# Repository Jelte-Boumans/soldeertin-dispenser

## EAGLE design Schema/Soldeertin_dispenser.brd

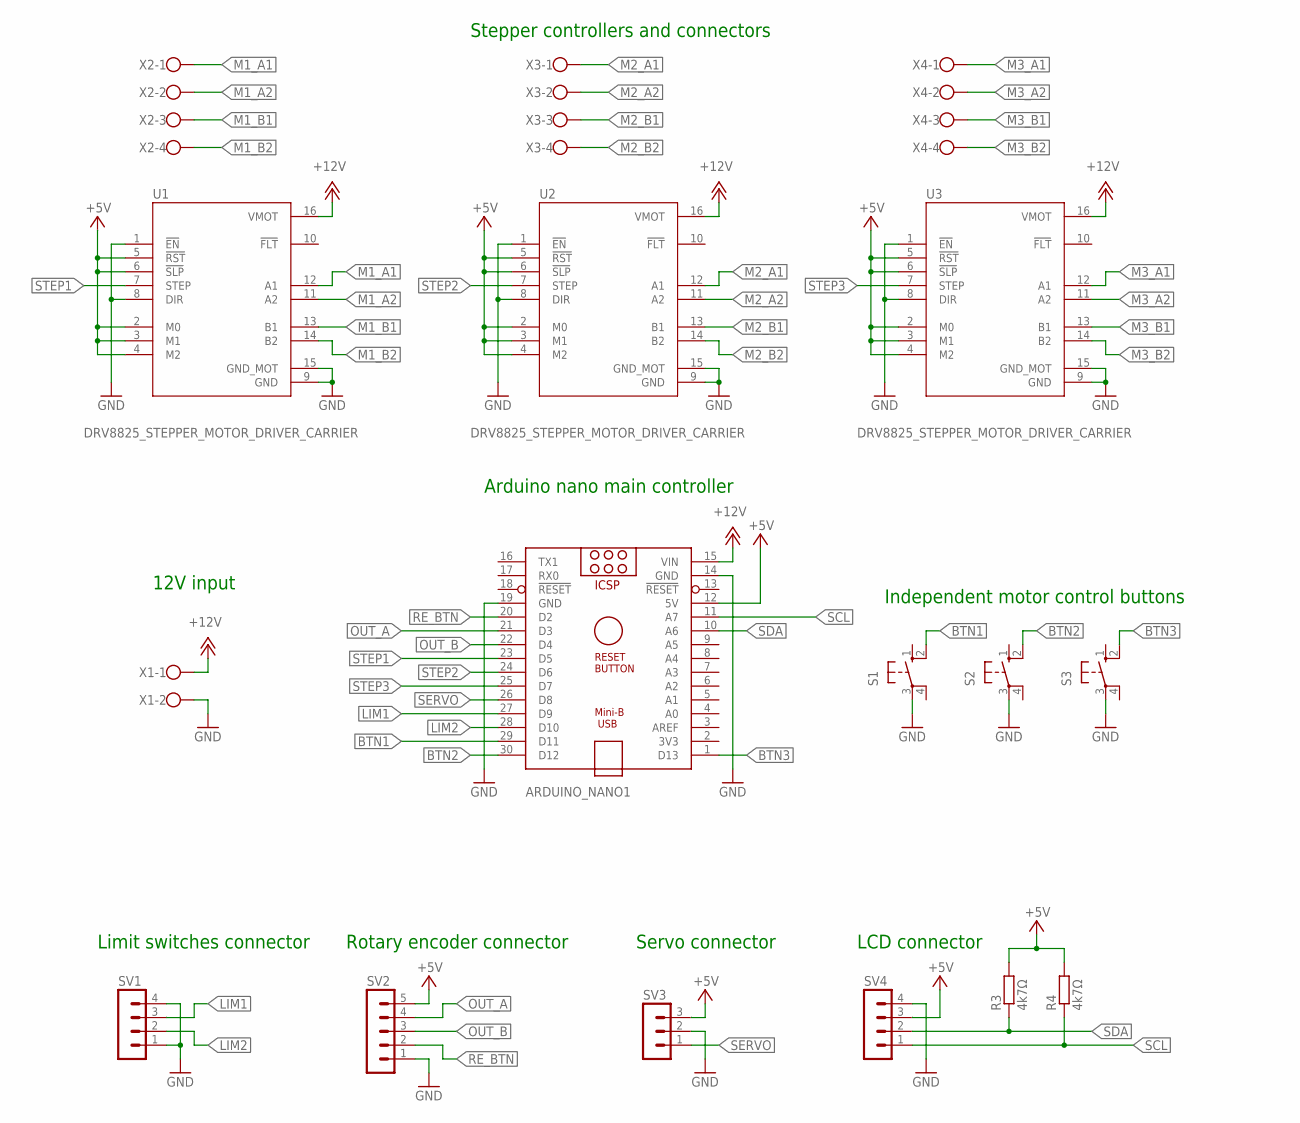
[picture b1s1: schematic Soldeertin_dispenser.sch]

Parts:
ARDUINO_NANO1: ARDUINO_NANO
R3, R4: 4k7Ω; 0207/10
S1, S2, S3: 10-XX; B3F-10XX
SV1, SV4: MA04-1
SV2: MA05-1
SV3: MA03-1
U1, U2, U3: DRV8825_STEPPER_MOTOR_DRIVER_CARRIER; IC_DRV8825_STEPPER_MOTOR_DRIVER_CARRIER
X1: W237-102
X2, X3, X4: W237-4

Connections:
+5V: ARDUINO_NANO1.12 (5V), R3.2, R4.2, SV2.5, SV3.3, SV4.3, U1.2 (M0), U1.3 (M1), U1.4 (M2), U1.5 (!RST), U1.6 (!SLP), U2.2 (M0), U2.3 (M1), U2.4 (M2), U2.5 (!RST), U2.6 (!SLP), U3.2 (M0), U3.3 (M1), U3.4 (M2), U3.5 (!RST), U3.6 (!SLP)
+12V: ARDUINO_NANO1.15 (VIN), U1.16 (VMOT), U2.16 (VMOT), U3.16 (VMOT), X1.1
BTN1: ARDUINO_NANO1.29 (D11), S1.2 (S1)
BTN2: ARDUINO_NANO1.30 (D12), S2.2 (S1)
BTN3: ARDUINO_NANO1.1 (D13), S3.2 (S1)
GND: ARDUINO_NANO1.14 (GND), ARDUINO_NANO1.19 (GND), S1.3, S2.3, S3.3, SV1.1, SV1.4, SV2.1, SV3.2, SV4.4, U1.1 (!EN), U1.8 (DIR), U1.9 (GND), U1.15 (GND_MOT), U2.1 (!EN), U2.8 (DIR), U2.9 (GND), U2.15 (GND_MOT), U3.1 (!EN), U3.8 (DIR), U3.9 (GND), U3.15 (GND_MOT), X1.2
LIM1: ARDUINO_NANO1.27 (D9), SV1.3
LIM2: ARDUINO_NANO1.28 (D10), SV1.2
M1_A1: U1.12 (A1), X2.1
M1_A2: U1.11 (A2), X2.2
M1_B1: U1.13 (B1), X2.3
M1_B2: U1.14 (B2), X2.4
M2_A1: U2.12 (A1), X3.1
M2_A2: U2.11 (A2), X3.2
M2_B1: U2.13 (B1), X3.3
M2_B2: U2.14 (B2), X3.4
M3_A1: U3.12 (A1), X4.1
M3_A2: U3.11 (A2), X4.2
M3_B1: U3.13 (B1), X4.3
M3_B2: U3.14 (B2), X4.4
OUT_A: ARDUINO_NANO1.21 (D3), SV2.4
OUT_B: ARDUINO_NANO1.22 (D4), SV2.3
RE_BTN: ARDUINO_NANO1.20 (D2), SV2.2
SCL: ARDUINO_NANO1.11 (A7), R4.1, SV4.1
SDA: ARDUINO_NANO1.10 (A6), R3.1, SV4.2
SERVO: ARDUINO_NANO1.26 (D8), SV3.1
STEP1: ARDUINO_NANO1.23 (D5), U1.7 (STEP)
STEP2: ARDUINO_NANO1.24 (D6), U2.7 (STEP)
STEP3: ARDUINO_NANO1.25 (D7), U3.7 (STEP)

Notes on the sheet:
LCD connector
Limit switches connector
Rotary encoder connector
Servo connector
12V input
Arduino nano main controller
Independent motor control buttons
Stepper controllers and connectors

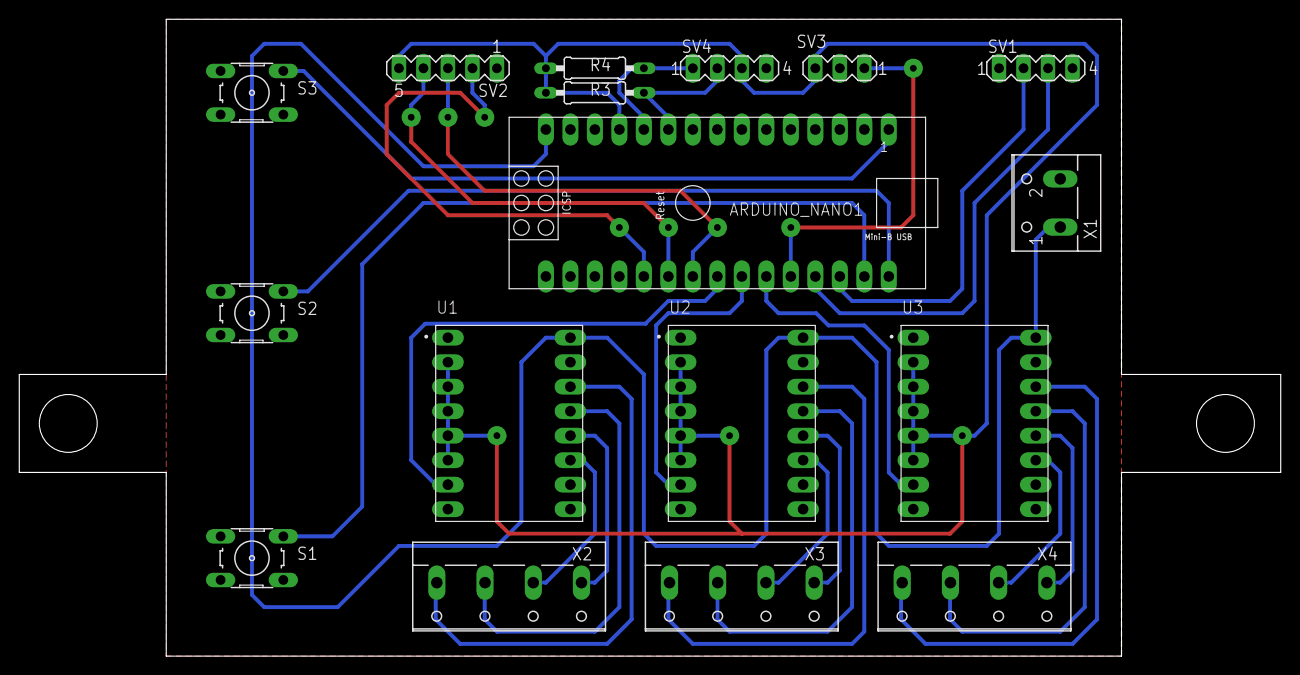
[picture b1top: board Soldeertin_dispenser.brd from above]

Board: 2 copper layers, 130.8 x 66.0 mm, 17 parts (0 on the bottom side), 29 nets.

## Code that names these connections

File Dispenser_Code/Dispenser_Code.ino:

// Soldeertin dispenseer
// Made by Jelte Boumans 2021-2022
#include <LiquidCrystal_I2C.h>
#include <Servo.h>
#include <BasicEncoder.h>

// Rotary encoder pins
#define RE_BUTTON 2
#define RE_A 3
#define RE_B 4

// DRV8825 Step pins
#define STEP1 5
#define STEP2 6
#define STEP3 7

// Servo pin
#define SERVO 8

// Limit switches pins
#define LIM1 9
#define LIM2 10

// Manual motor control buttons
#define BTN1 11
#define BTN2 12
#define BTN3 13

// Min and max length of a dispensed wire
#define MAX_LEN 50
#define MIN_LEN 5

// Values to open or close scissor
#define SERVO_OPEN 180
#define SERVO_CLOSE 0

// Delay when going to another state
#define NEXT_STATE_DELAY 250

// The ammount of steps it takes to extrude 1cm of wire (with microstep en 10µs delay)
#define STEPS_PER_CM 4500L

// Change this from true to false to disable the lidOpen function
// Set this to false when debugging
#define ENABLE_LID_SECURITY true

Servo myServo;
LiquidCrystal_I2C lcd(0x27,16,2);
BasicEncoder encoder(RE_A, RE_B);

enum States {
  mainmenu,
  motorcontrol,
  selectDiameter,
  selectLength,
  dispense,
  cut
};

States state = mainmenu;

byte selectedDiameter = 0;
byte selectedLength = MIN_LEN;

void setup() { 
  pinMode(RE_A, INPUT);
  pinMode(RE_B, INPUT);
  pinMode(RE_BUTTON, INPUT_PULLUP);

  pinMode(STEP1, OUTPUT);
  pinMode(STEP2, OUTPUT);
  pinMode(STEP3, OUTPUT);

  pinMode(SERVO, OUTPUT);

  pinMode(LIM1, INPUT_PULLUP);
  pinMode(LIM2, INPUT_PULLUP);

  pinMode(BTN1, INPUT_PULLUP);
  pinMode(BTN2, INPUT_PULLUP);
  pinMode(BTN3, INPUT_PULLUP);

  myServo.attach(SERVO);
  myServo.write(SERVO_OPEN);

  lcd.init();
  lcd.backlight();
  lcd.clear();

  setup_encoders(RE_A,RE_B);

  digitalWrite(STEP1, LOW); // Start with all step pins low
  digitalWrite(STEP2, LOW);
  digitalWrite(STEP3, LOW);
}

void loop() {
  switch(state) {
    case mainmenu:
      f_mainmenu();
      break;

    case motorcontrol:
      f_motorcontrol();
      break;

    case selectDiameter:
      f_selectDiameter();
      break;

    case selectLength:
      f_selectLength();
      break;

    case dispense:
      f_dispense();
      break;

    case cut:
      f_cut();
      break;
  }
}

bool yCord = 0;
void f_mainmenu() {
  lcd.setCursor(0,0);
  lcd.print("Dispenser");
  lcd.setCursor(0,1);
  lcd.print("Change roll");

  int encoder_change = encoder.get_change();
  if(encoder_change) {  // Move cursor position when you turn the RE
    yCord = !yCord;
    encoder_change = 0;
  }

  lcd.setCursor(15,yCord);  // Print cursor
  lcd.print("<");
  lcd.setCursor(15,!yCord);
  lcd.print(" ");
    
  
  if(!digitalRead(RE_BUTTON)) { // When the RE is pressed go to the next state depending on the cursor position
    if(yCord == 0)
      state = selectDiameter;
    else
      state = motorcontrol;

    lcd.clear();  // Clear LCD for next state
    delay(NEXT_STATE_DELAY);  // Delay so you dont skip states when RE is pressed
  }
}

byte stepPin = 0;
void f_motorcontrol() {
  lcd.setCursor(0,0);
  lcd.print("    Press RE    ");
  lcd.setCursor(0,1);
  lcd.print("   to go back   ");

  if(!digitalRead(BTN1))  // The step pin that is used will change depending on which button is pressed
    stepPin = STEP1;
  else if(!digitalRead(BTN2))
    stepPin = STEP2;
//  else if(!digitalRead(BTN3))
//    stepPin = STEP3;
  else
    stepPin = 0;

  while(stepPin) { // If one of the buttons is pressed, send pulses to the selected step pin
    digitalWrite(stepPin, !digitalRead(stepPin));
    delayMicroseconds(10);

    if(digitalRead(BTN1) && digitalRead(BTN2))
      stepPin = 0;
    }

  
  if(!digitalRead(RE_BUTTON)) { // When the RE is pressed go back to the main menu
    state = mainmenu;
    lcd.clear();  // Clear LCD for next state
    delay(NEXT_STATE_DELAY);  // Delay so you dont skip states when RE is pressed
  }
}

byte xCord = 3;
void f_selectDiameter() {
  lcd.setCursor(0,0);
  lcd.print("  Diameter(mm)  ");
  lcd.setCursor(0,1);
  lcd.print("0.3   0.6   1.0 ");

  // If RE is turned CW
  int encoder_change = encoder.get_change();
  if(encoder_change >= 1) {
    if(xCord >= 15)  // Move cursor to the right
      xCord = 3;
    else
      xCord += 6; 
    encoder_change = 0;
  }

  // If RE is turned CCW
  else if(encoder_change <= -1) {
    if(xCord <= 3)  // Move cursor to the left
      xCord = 15;
    else
      xCord -= 6; 
    encoder_change = 0;
  }

  lcd.setCursor(xCord,1); // Print cursor
  lcd.print("<");

  if(!digitalRead(RE_BUTTON)) { // When the RE is pressed save the selected diameter the cursor was on
    if(xCord == 3)
      selectedDiameter = 1;
    else if (xCord == 9)
      selectedDiameter = 2;
    else if (xCord == 15)
      selectedDiameter = 3;

    xCord = 3;  // Reset variable for next time
    state = selectLength;
    lcd.clear();  // Clear LCD for next state
    delay(NEXT_STATE_DELAY);  // Delay so you dont skip states when RE is pressed
  }
}

void f_selectLength() {
  lcd.setCursor(3,0);
  lcd.print("Length(cm)");
  lcd.setCursor(7,1);
  lcd.print("=  ");

  // If RE is turned
  int encoder_change = encoder.get_change();
  if(encoder_change) {
    if(encoder_change >= 1) // If RE is turned CW
      selectedLength++;
    else if(encoder_change <= -1) // If RE is turned CCW
      selectedLength--;

    if(selectedLength > MAX_LEN) // Limit length value
      selectedLength = MIN_LEN;
    else if(selectedLength < MIN_LEN)
      selectedLength = MAX_LEN;
  }

  lcd.setCursor(8,1); // Print selected length
  lcd.print(selectedLength);

  if(!digitalRead(RE_BUTTON)) { // When the RE is pressed start dispensing the selected length
    state = dispense;
    lcd.clear();  // Clear LCD for next state
    delay(NEXT_STATE_DELAY);  // Delay so you dont skip states when RE is pressed
  }
}

void f_dispense() {
  lcd.setCursor(2,0);
  lcd.print("Dispensing...");
  
  if(selectedDiameter == 1)
    stepPin = STEP1;
  else if (selectedDiameter == 2)
    stepPin = STEP2;
  else if (selectedDiameter == 3)
    stepPin = STEP3;

  for(unsigned long i = 0; i < selectedLength*STEPS_PER_CM; i++) {
    if((!digitalRead(LIM1) || !digitalRead(LIM2)) && ENABLE_LID_SECURITY) {  // If lid is opened, stop dispending
      lidOpen();
      lcd.setCursor(2,0);
      lcd.print("Dispensing...");
    }    
              
    digitalWrite(stepPin, !digitalRead(stepPin));
    delayMicroseconds(10);
  }

  selectedLength = MIN_LEN; // Reset variables for next time

  state = cut;
  lcd.clear();  // Clear LCD for next state
  delay(NEXT_STATE_DELAY);  // Delay so you dont skip states when RE is pressed
}

void f_cut() {
  lcd.setCursor(3,0);
  lcd.print("Cutting...");
  
  for(byte i = 0; i < 3; i++) { // Open and close scissor 3 times
    if((!digitalRead(LIM1) || !digitalRead(LIM2)) && ENABLE_LID_SECURITY) {  // If lid is opened, stop cutting
      lidOpen();
      lcd.setCursor(3,0);
      lcd.print("Cutting...");
    }   
      
    myServo.write(SERVO_CLOSE);
    delay(600);
    myServo.write(SERVO_OPEN);
    delay(600);
  }

  for(unsigned long i = 0; i < 3*STEPS_PER_CM; i++) {  // Dispense a little bit of wire to set it up for the next time
    if((!digitalRead(LIM1) || !digitalRead(LIM2)) && ENABLE_LID_SECURITY) {  // If lid is opened, stop dispending
      lidOpen();
      lcd.setCursor(3,0);
      lcd.print("Cutting...");
    }    
              
    digitalWrite(stepPin, !digitalRead(stepPin));
    delayMicroseconds(10);
  }

  state = mainmenu;
  lcd.clear();  // Clear LCD for next state
  delay(NEXT_STATE_DELAY);  // Delay so you dont skip states when RE is pressed
}

void lidOpen() {
  lcd.clear();
  while(!digitalRead(LIM1) || !digitalRead(LIM2)) { // Dont exit this function until the lid is closed
    lcd.setCursor(4,0);
    lcd.print("Close lid");
    lcd.setCursor(3,1);
    lcd.print("to continue");
  }
  
  lcd.clear();  // Clear LCD for next state
  delay(NEXT_STATE_DELAY);  // Delay so you dont skip states when RE is pressed
}

void pciSetup(byte pin) { // Setup pin change interupt on pin
  *digitalPinToPCMSK(pin) |= bit(digitalPinToPCMSKbit(pin));  // enable pin
  PCIFR |= bit(digitalPinToPCICRbit(pin));  // clear outstanding interrupt
  PCICR |= bit(digitalPinToPCICRbit(pin));  // enable interrupt for group
}

void setup_encoders(int a, int b) {
  uint8_t old_sreg = SREG;  // save the current interrupt enable flag
  noInterrupts();
  pciSetup(a);
  pciSetup(b);
  encoder.reset();
  SREG = old_sreg;  // restore the previous interrupt enable flag state
}

ISR(PCINT2_vect) {  // pin change interrupt for D0 to D7
  encoder.service();
}
